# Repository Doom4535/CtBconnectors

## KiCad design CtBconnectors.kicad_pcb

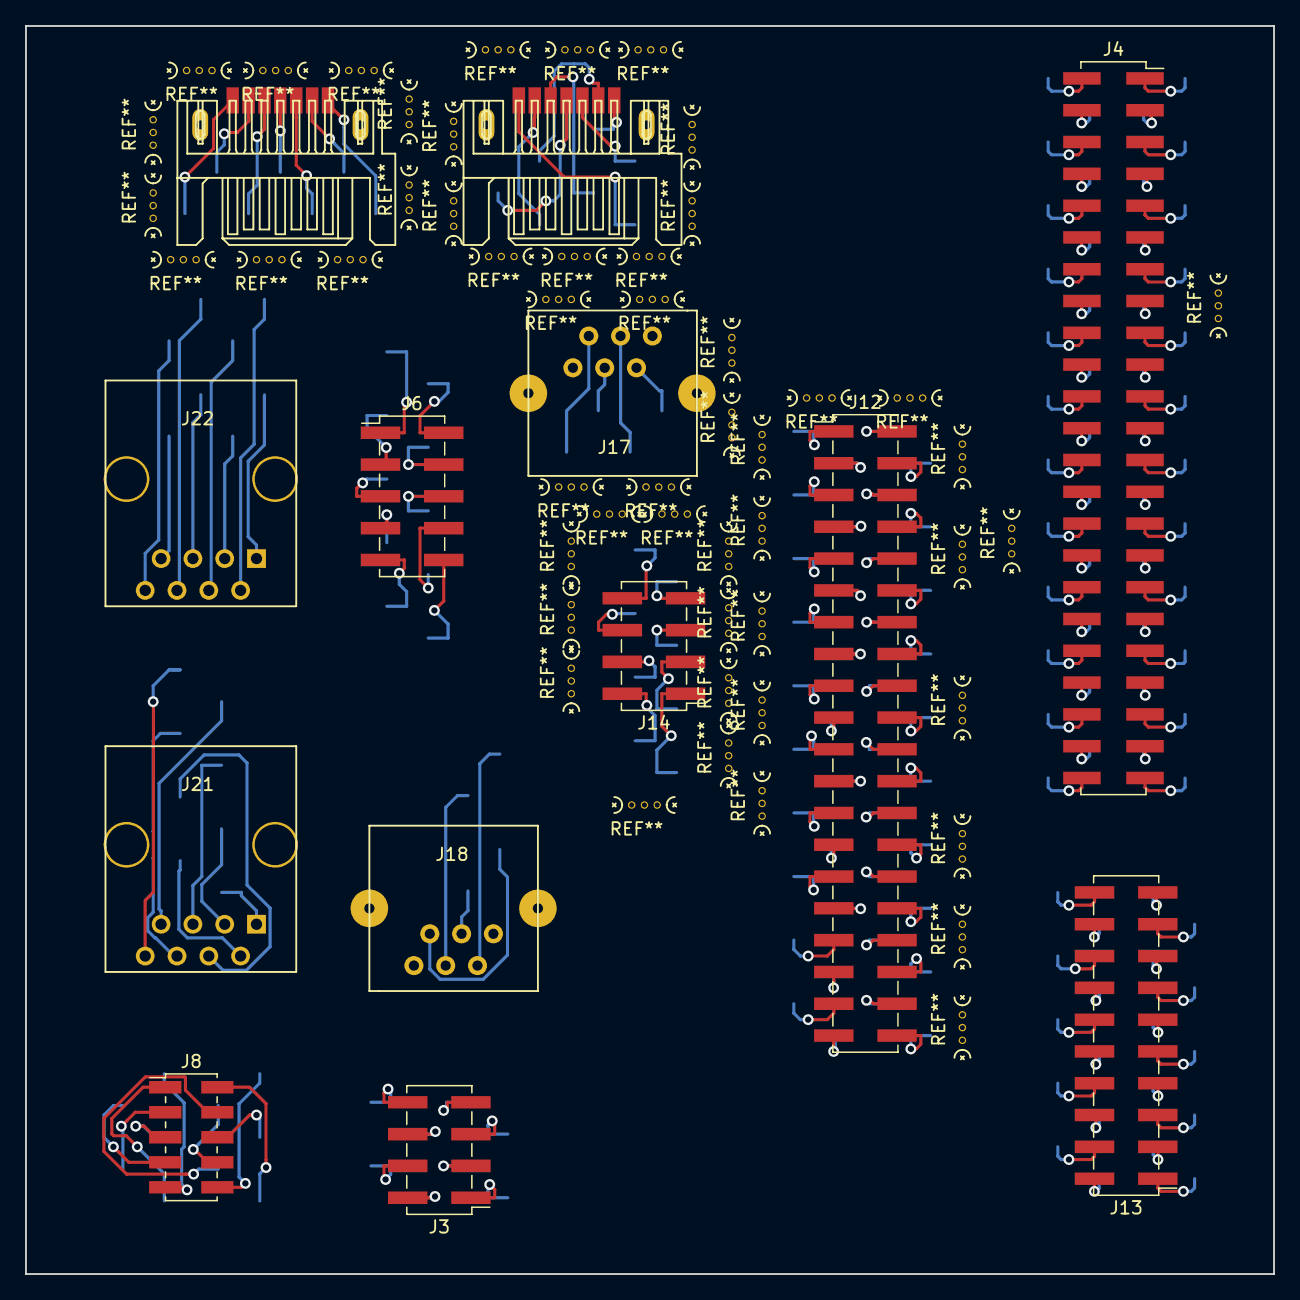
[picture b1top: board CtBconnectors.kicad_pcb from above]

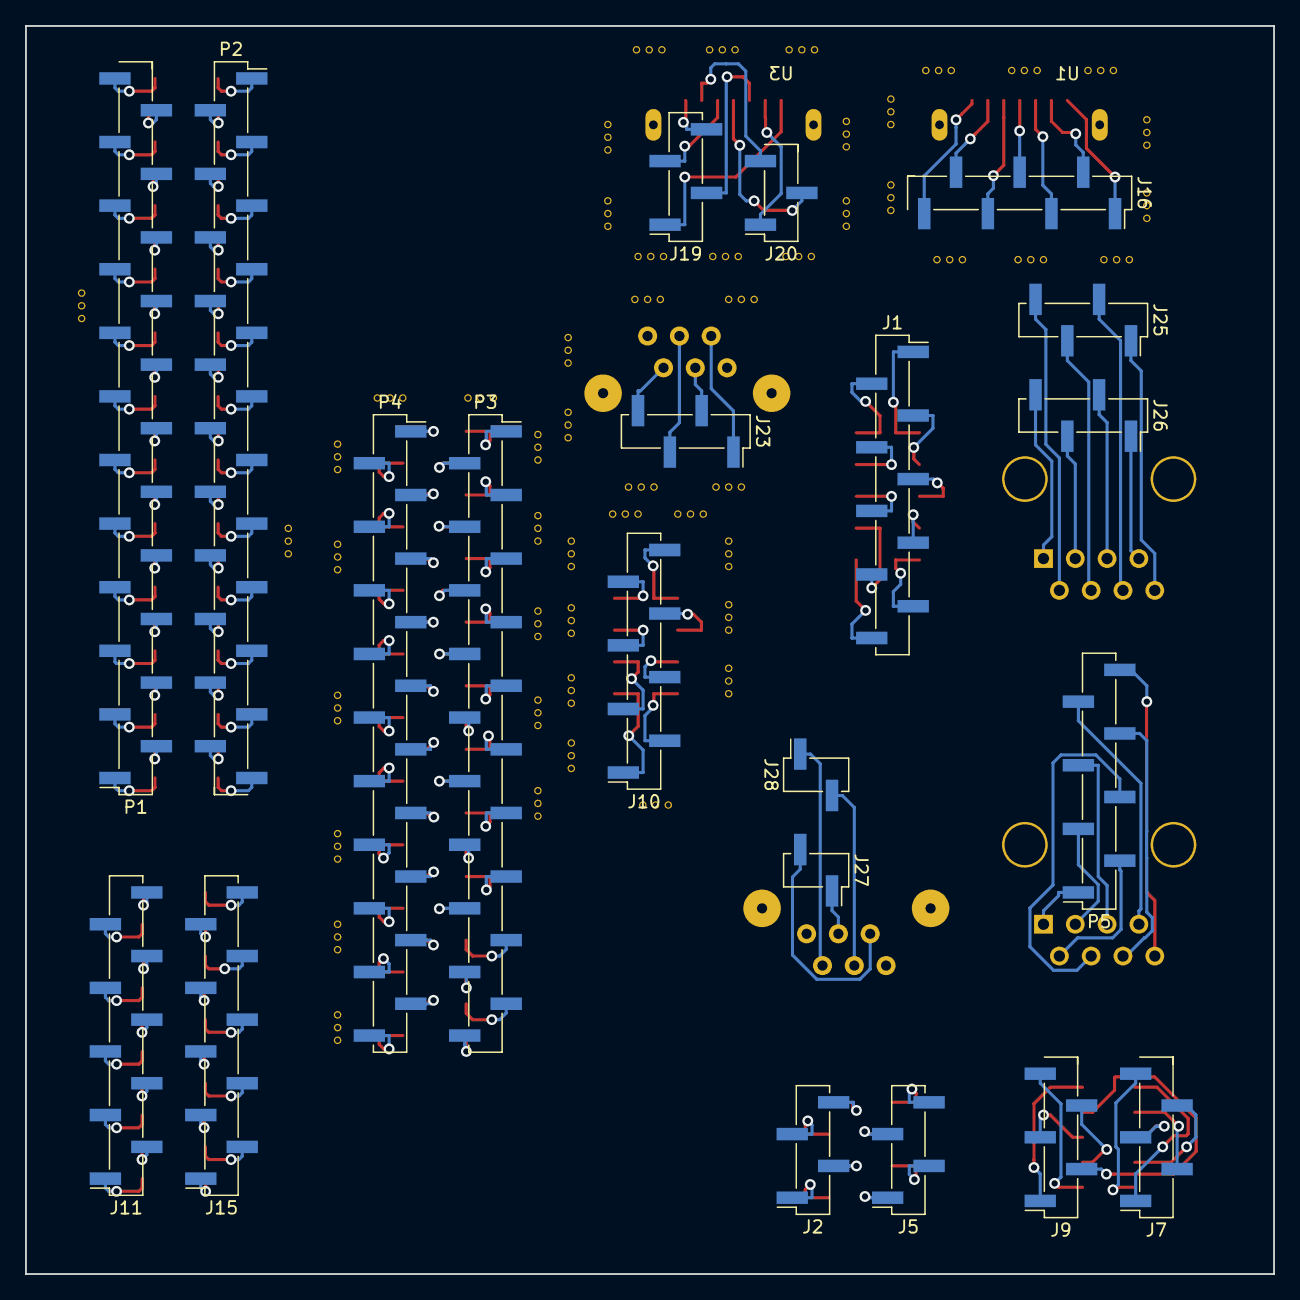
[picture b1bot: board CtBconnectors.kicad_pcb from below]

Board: 2 copper layers, 99.7 x 99.7 mm, 34 parts (21 on the bottom side), 180 nets.

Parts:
J1: Conn_01x10_Male; Pin_Header_Straight_1x10_Pitch2.54mm_SMD_Pin1Right
J2, J19, J25: Conn_01x04_Male_Odd; Pin_Header_Straight_1x04_Pitch2.54mm_SMD_Pin1Right
J3, J14: Conn_02x04_Odd_Even; Pin_Header_Straight_2x04_Pitch2.54mm_SMD
J4: Conn_02x23_Odd_Even; Socket_Strip_Straight_2x23_Pitch2.54mm_SMD
J5, J26: Conn_01x04_Male_Even; Pin_Header_Straight_1x04_Pitch2.54mm_SMD_Pin1Right
J6: Conn_02x05_Odd_Even; Pin_Header_Straight_2x05_Pitch2.54mm_SMD
J7: Conn_01x05_Male_Odd; Pin_Header_Straight_1x05_Pitch2.54mm_SMD_Pin1Right
J8: Conn_02x05_Odd_Even_2mm; Pin_Header_Straight_2x05_Pitch2.00mm_SMD
J9: Conn_01x05_Male_Even; Pin_Header_Straight_1x05_Pitch2.54mm_SMD_Pin1Right
J10: Conn_01x08_Male; Pin_Header_Straight_1x08_Pitch2.54mm_SMD_Pin1Right
J11: Conn_01x10_Male_Odd; Pin_Header_Straight_1x10_Pitch2.54mm_SMD_Pin1Right
J12: Conn_02x20_Odd_Even; Pin_Header_Straight_2x20_Pitch2.54mm_SMD
J13: Conn_02x10_Odd_Even; Pin_Header_Straight_2x10_Pitch2.54mm_SMD
J15: Conn_01x10_Male_Even; Pin_Header_Straight_1x10_Pitch2.54mm_SMD_Pin1Right
J16: Conn_01x07_Male; Pin_Header_Straight_1x07_Pitch2.54mm_SMD_Pin1Right
J17, J18: RJ12; RJ12_E
J20: Conn_01x03_Male_Even; Pin_Header_Straight_1x03_Pitch2.54mm_SMD_Pin1Right
J21, J22: RJ45_8
J23: Conn_01x04_Male; Pin_Header_Straight_1x04_Pitch2.54mm_SMD_Pin1Right
J27: Conn_01x02_Male_Even; Pin_Header_Straight_1x02_Pitch2.54mm_SMD_Pin1Right
J28: Conn_01x02_Male_Odd; Pin_Header_Straight_1x02_Pitch2.54mm_SMD_Pin1Right
P1: CONN_01X23_Odd; Pin_Header_Straight_1x23_Pitch2.54mm_SMD_Pin1Right
P2: CONN_01X23_Even; Pin_Header_Straight_1x23_Pitch2.54mm_SMD_Pin1Right
P3: CONN_01X20_Odd; Pin_Header_Straight_1x20_Pitch2.54mm_SMD_Pin1Right
P4: CONN_01X20_Even; Pin_Header_Straight_1x20_Pitch2.54mm_SMD_Pin1Right
P5: CONN_01X08; Pin_Header_Straight_1x08_Pitch2.54mm_SMD_Pin1Right
U1, U3: SATA_data; SATA-7_SMD

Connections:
unnamed: J2.1, J3.1
unnamed: J2.2, J3.3
unnamed: J2.3, J3.5
unnamed: J2.4, J3.7
unnamed: J3.2, J5.1
unnamed: J3.4, J5.2
unnamed: J3.6, J5.3
unnamed: J3.8, J5.4
unnamed: J4.1, P1.23
unnamed: J4.2, P2.1
unnamed: J4.3, P1.22
unnamed: J4.4, P2.2
unnamed: J4.5, P1.21
unnamed: J4.6, P2.3
unnamed: J4.7, P1.20
unnamed: J4.8, P2.4
unnamed: J4.9, P1.19
unnamed: J4.10, P2.5
unnamed: J4.11, P1.18
unnamed: J4.12, P2.6
unnamed: J4.13, P1.17
unnamed: J4.14, P2.7
unnamed: J4.15, P1.16
unnamed: J4.16, P2.8
unnamed: J4.17, P1.15
unnamed: J4.18, P2.9
unnamed: J4.19, P1.14
unnamed: J4.20, P2.10
unnamed: J4.21, P1.13
unnamed: J4.22, P2.11
unnamed: J4.23, P1.12
unnamed: J4.24, P2.12
unnamed: J4.25, P1.11
unnamed: J4.26, P2.13
unnamed: J4.27, P1.10
unnamed: J4.28, P2.14
unnamed: J4.29, P1.9
unnamed: J4.30, P2.15
unnamed: J4.31, P1.8
unnamed: J4.32, P2.16
unnamed: J4.33, P1.7
unnamed: J4.34, P2.17
unnamed: J4.35, P1.6
unnamed: J4.36, P2.18
unnamed: J4.37, P1.5
unnamed: J4.38, P2.19
unnamed: J4.39, P1.4
unnamed: J4.40, P2.20
unnamed: J4.41, P1.3
unnamed: J4.42, P2.21
unnamed: J4.43, P1.2
unnamed: J4.44, P2.22
unnamed: J4.45, P1.1
unnamed: J4.46, P2.23
unnamed: J7.1, J8.1
unnamed: J7.2, J8.3
unnamed: J7.3, J8.5
unnamed: J7.4, J8.7
unnamed: J7.5, J8.9
unnamed: J8.2, J9.1
unnamed: J8.4, J9.2
unnamed: J8.6, J9.3
unnamed: J8.8, J9.4
unnamed: J8.10, J9.5
unnamed: J11.1, J13.1
unnamed: J11.2, J13.3
unnamed: J11.3, J13.5
unnamed: J11.4, J13.7
unnamed: J11.5, J13.9
unnamed: J11.6, J13.11
unnamed: J11.7, J13.13
unnamed: J11.8, J13.15
unnamed: J11.9, J13.17
unnamed: J11.10, J13.19
unnamed: J12.1, P3.1
unnamed: J12.2, P4.1
unnamed: J12.3, P3.2
unnamed: J12.4, P4.2
unnamed: J12.5, P3.3
unnamed: J12.6, P4.3
unnamed: J12.7, P3.4
unnamed: J12.8, P4.4
unnamed: J12.9, P3.5
unnamed: J12.10, P4.5
unnamed: J12.11, P3.6
unnamed: J12.12, P4.6
unnamed: J12.13, P3.7
unnamed: J12.14, P4.7
unnamed: J12.15, P3.8
unnamed: J12.16, P4.8
unnamed: J12.17, P3.9
unnamed: J12.18, P4.9
unnamed: J12.19, P3.10
unnamed: J12.20, P4.10
unnamed: J12.21, P3.11
unnamed: J12.22, P4.11
unnamed: J12.23, P3.12
unnamed: J12.24, P4.12
unnamed: J12.25, P3.13
unnamed: J12.26, P4.13
unnamed: J12.27, P3.14
unnamed: J12.28, P4.14
unnamed: J12.29, P3.15
unnamed: J12.30, P4.15
unnamed: J12.31, P3.16
unnamed: J12.32, P4.16
unnamed: J12.33, P3.17
unnamed: J12.34, P4.17
unnamed: J12.35, P3.18
unnamed: J12.36, P4.18
unnamed: J12.37, P3.19
unnamed: J12.38, P4.19
unnamed: J12.39, P3.20
unnamed: J12.40, P4.20
unnamed: J13.2, J15.1
unnamed: J13.4, J15.2
unnamed: J13.6, J15.3
unnamed: J13.8, J15.4
unnamed: J13.10, J15.5
unnamed: J13.12, J15.6
unnamed: J13.14, J15.7
unnamed: J13.16, J15.8
unnamed: J13.18, J15.9
unnamed: J13.20, J15.10
unnamed: J16.1, U1.1
unnamed: J16.2, U1.2
unnamed: J16.3, U1.3
unnamed: J16.4, U1.4
unnamed: J16.5, U1.5
unnamed: J16.6, U1.6
unnamed: J16.7, U1.7
unnamed: J17.2, J23.1
unnamed: J17.3, J23.2
unnamed: J17.4, J23.3
unnamed: J17.5, J23.4
unnamed: J18.2, J28.1
unnamed: J18.3, J27.1
unnamed: J18.4, J28.2
unnamed: J18.5, J27.2
unnamed: J19.1, U3.1
unnamed: J19.2, U3.3
unnamed: J19.3, U3.5
unnamed: J19.4, U3.7
unnamed: J20.1, U3.2
unnamed: J20.2, U3.4
unnamed: J20.3, U3.6
unnamed: J21.1, P5.1
unnamed: J21.2, P5.2
unnamed: J21.3, P5.3
unnamed: J21.4, P5.4
unnamed: J21.5, P5.5
unnamed: J21.6, P5.6
unnamed: J21.7, P5.7
unnamed: J21.8, P5.8
unnamed: J22.1, J26.4
unnamed: J22.2, J25.4
unnamed: J22.3, J26.3
unnamed: J22.4, J25.3
unnamed: J22.5, J26.2
unnamed: J22.6, J25.2
unnamed: J22.7, J26.1
unnamed: J22.8, J25.1
P1_2x4_1x8_L: J10.1, J14.1
P1_2x5_1x10_L: J1.1, J6.1
P2_2x4_1x8_L: J10.2, J14.2
P2_2x5_1x10_L: J1.2, J6.2
P3_2x4_1x8_L: J10.3, J14.3
P3_2x5_1x10_L: J1.3, J6.3
P4_2x4_1x8_L: J10.4, J14.4
P4_2x5_1x10_L: J1.4, J6.4
P5_2x4_1x8_L: J10.5, J14.5
P5_2x5_1x10_L: J1.5, J6.5
P6_2x4_1x8_L: J10.6, J14.6
P6_2x5_1x10_L: J1.6, J6.6
P7_2x4_1x8_L: J10.7, J14.7
P7_2x5_1x10_L: J1.7, J6.7
P8_2x4_1x8_L: J10.8, J14.8
P8_2x5_1x10_L: J1.8, J6.8
P9_2x5_1x10_L: J1.9, J6.9
P10_2x5_1x10_L: J1.10, J6.10

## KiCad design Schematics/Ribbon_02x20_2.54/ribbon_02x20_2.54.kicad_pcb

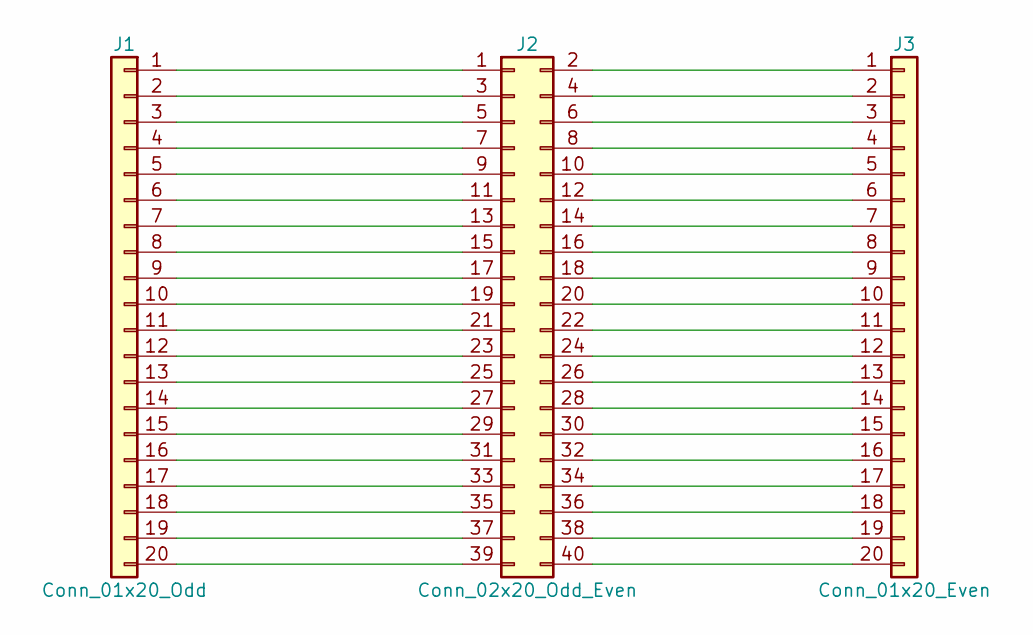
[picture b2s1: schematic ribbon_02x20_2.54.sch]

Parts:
J1: Conn_01x20_Odd; Pin_Header_Straight_1x20_Pitch2.54mm_SMD_Pin1Right
J2: Conn_02x20_Odd_Even; Socket_Strip_Straight_2x20_Pitch2.54mm_SMD
J3: Conn_01x20_Even; Pin_Header_Straight_1x20_Pitch2.54mm_SMD_Pin1Right

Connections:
unnamed: J1.1, J2.1
unnamed: J1.2, J2.3
unnamed: J1.3, J2.5
unnamed: J1.4, J2.7
unnamed: J1.5, J2.9
unnamed: J1.6, J2.11
unnamed: J1.7, J2.13
unnamed: J1.8, J2.15
unnamed: J1.9, J2.17
unnamed: J1.10, J2.19
unnamed: J1.11, J2.21
unnamed: J1.12, J2.23
unnamed: J1.13, J2.25
unnamed: J1.14, J2.27
unnamed: J1.15, J2.29
unnamed: J1.16, J2.31
unnamed: J1.17, J2.33
unnamed: J1.18, J2.35
unnamed: J1.19, J2.37
unnamed: J1.20, J2.39
unnamed: J2.2, J3.1
unnamed: J2.4, J3.2
unnamed: J2.6, J3.3
unnamed: J2.8, J3.4
unnamed: J2.10, J3.5
unnamed: J2.12, J3.6
unnamed: J2.14, J3.7
unnamed: J2.16, J3.8
unnamed: J2.18, J3.9
unnamed: J2.20, J3.10
unnamed: J2.22, J3.11
unnamed: J2.24, J3.12
unnamed: J2.26, J3.13
unnamed: J2.28, J3.14
unnamed: J2.30, J3.15
unnamed: J2.32, J3.16
unnamed: J2.34, J3.17
unnamed: J2.36, J3.18
unnamed: J2.38, J3.19
unnamed: J2.40, J3.20

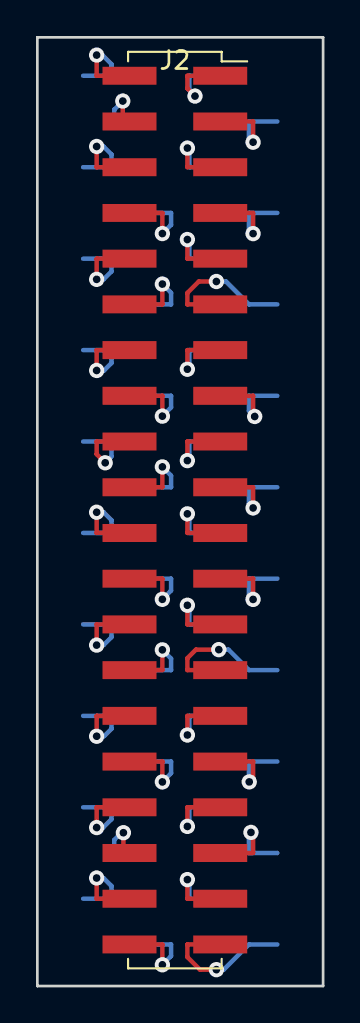
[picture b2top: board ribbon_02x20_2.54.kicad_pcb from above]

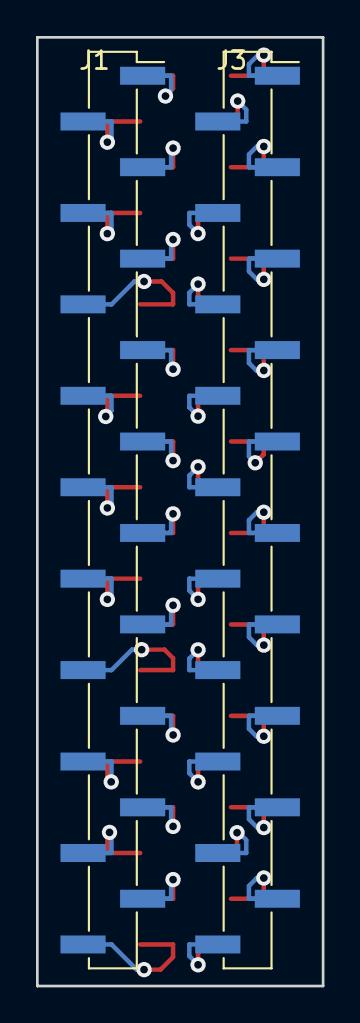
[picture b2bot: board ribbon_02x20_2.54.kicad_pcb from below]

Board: 2 copper layers, 15.9 x 52.7 mm, 3 parts (2 on the bottom side), 40 nets.
